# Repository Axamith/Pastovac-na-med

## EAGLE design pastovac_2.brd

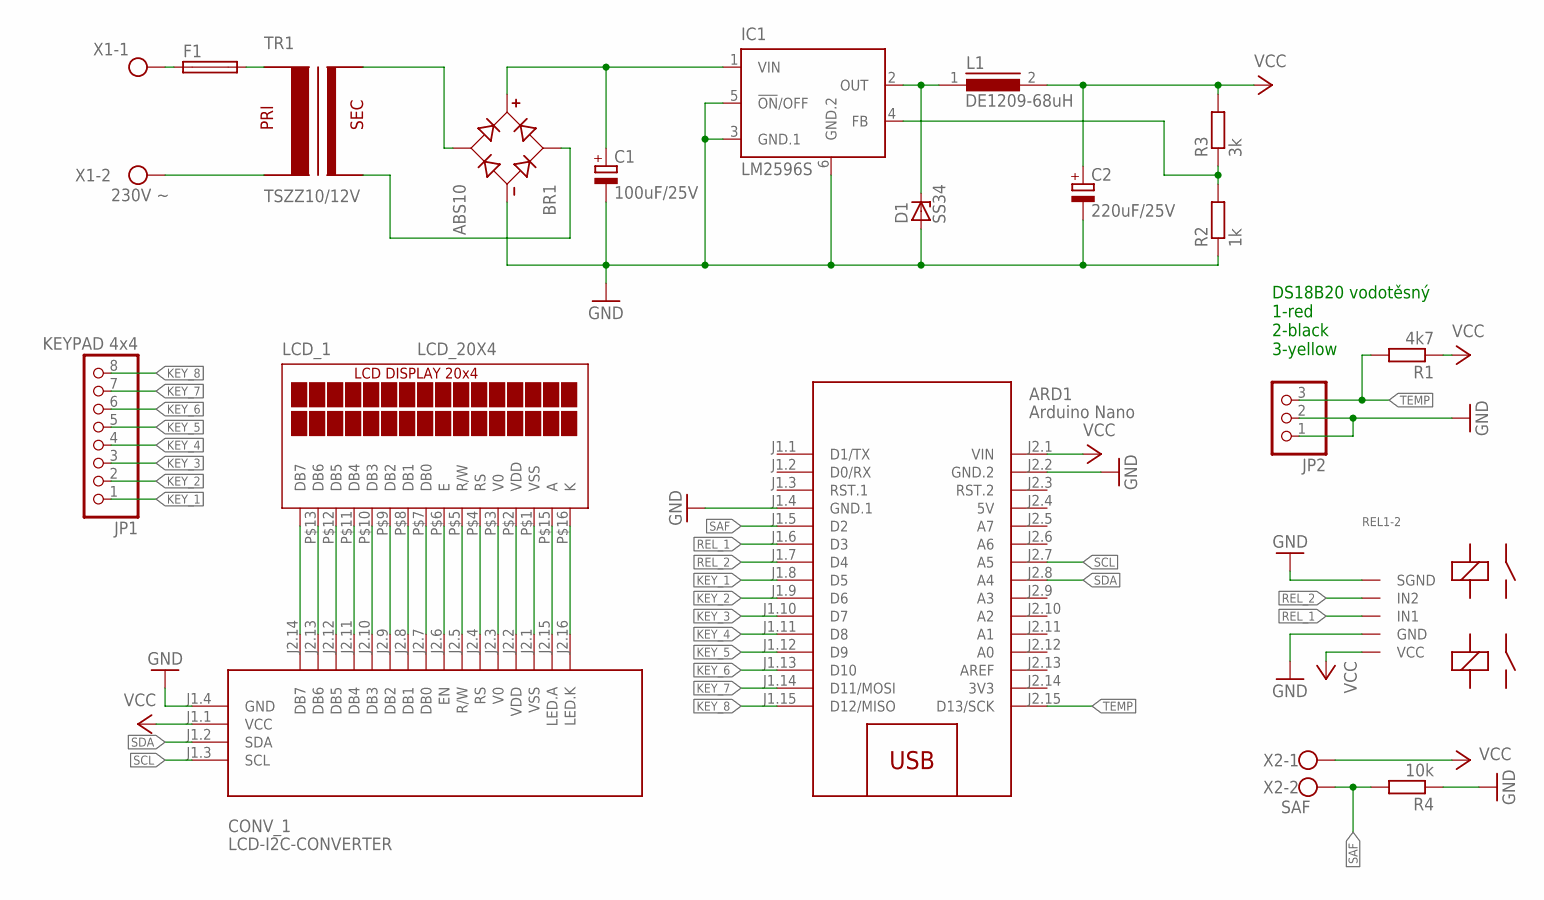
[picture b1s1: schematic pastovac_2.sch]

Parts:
ARD1: Arduino Nano; ARDUINO-NANO-3.0
BR1: ABS10; SOT200P640X160-4N
C1: 100uF/25V; 140CLH-0810
C2: 220uF/25V; 140CLH-0810
CONV_1: LCD-I2C-CONVERTER
D1: SS34; DO214AC
F1: FUSEBLANK_5X20MM; FUSE_HOLDER_5X20MM
IC1: LM2596S; TO263-5
JP1: KEYPAD 4x4; 1X08
JP2: PINHD-1X3; 1X03
L1: DE1209-68uH; DR127
LCD_1: LCD_20X4
R1: 4k7; M1206
R2: 1k; M1206
R3: 3k; M1206
R4: 10k; M1206
REL1-2: RELAY-2-5V-30A
TR1: TSZZ10/12V; TSZZ12/007M
X1: 230V ~; W237-102
X2: SAF; W237-102

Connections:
3V3: ARD1.J2.14 (3V3)
5V: ARD1.J2.4 (5V)
GND: ARD1.J1.4 (GND.1), ARD1.J2.2 (GND.2), BR1.4 (-), C1.-, C2.-, CONV_1.J1.4 (GND), D1.A, IC1.3 (GND.1), IC1.5 (!ON!/OFF), IC1.6 (GND.2), JP2.1, JP2.2, R2.1, R4.1, REL1-2.GND, REL1-2.SGND
KEY_1: ARD1.J1.8 (D5), JP1.1
KEY_2: ARD1.J1.9 (D6), JP1.2
KEY_3: ARD1.J1.10 (D7), JP1.3
KEY_4: ARD1.J1.11 (D8), JP1.4
KEY_5: ARD1.J1.12 (D9), JP1.5
KEY_6: ARD1.J1.13 (D10), JP1.6
KEY_7: ARD1.J1.14 (D11/MOSI), JP1.7
KEY_8: ARD1.J1.15 (D12/MISO), JP1.8
unnamed: CONV_1.J2.14 (DB7), LCD_1.P$14 (DB7)
unnamed: CONV_1.J2.13 (DB6), LCD_1.P$13 (DB6)
unnamed: CONV_1.J2.12 (DB5), LCD_1.P$12 (DB5)
unnamed: CONV_1.J2.11 (DB4), LCD_1.P$11 (DB4)
unnamed: CONV_1.J2.10 (DB3), LCD_1.P$10 (DB3)
unnamed: CONV_1.J2.9 (DB2), LCD_1.P$9 (DB2)
unnamed: CONV_1.J2.8 (DB1), LCD_1.P$8 (DB1)
unnamed: CONV_1.J2.7 (DB0), LCD_1.P$7 (DB0)
unnamed: CONV_1.J2.6 (EN), LCD_1.P$6 (E)
unnamed: CONV_1.J2.5 (R/W), LCD_1.P$5 (R/W)
unnamed: CONV_1.J2.4 (RS), LCD_1.P$4 (RS)
unnamed: CONV_1.J2.3 (V0), LCD_1.P$3 (V0)
unnamed: CONV_1.J2.2 (VDD), LCD_1.P$2 (VDD)
unnamed: CONV_1.J2.1 (VSS), LCD_1.P$1 (VSS)
unnamed: CONV_1.J2.15 (LED.A), LCD_1.P$15 (A)
unnamed: CONV_1.J2.16 (LED.K), LCD_1.P$16 (K)
unnamed: D1.C, IC1.2 (OUT), L1.1
unnamed: BR1.1 (AC1), TR1.P$4
unnamed: IC1.4 (FB), R2.2, R3.1
unnamed: TR1.P$2, X1.2
unnamed: F1.2, TR1.P$1
unnamed: BR1.3 (+), C1.+, IC1.1 (VIN)
unnamed: F1.1, X1.1
unnamed: BR1.2 (AC2), TR1.P$3
REL_1: ARD1.J1.6 (D3), REL1-2.IN2 (IN1)
REL_2: ARD1.J1.7 (D4), REL1-2.IN1 (IN2)
SAF: ARD1.J1.5 (D2), R4.2, X2.2
SCL: ARD1.J2.7 (A5), CONV_1.J1.3 (SCL)
SDA: ARD1.J2.8 (A4), CONV_1.J1.2 (SDA)
TEMP: ARD1.J2.15 (D13/SCK), JP2.3, R1.2
VCC: ARD1.J2.1 (VIN), C2.+, CONV_1.J1.1 (VCC), L1.2, R1.1, R3.2, REL1-2.VCC, X2.1

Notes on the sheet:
DS18B20 vodotěsný 1-red 2-black 3-yellow

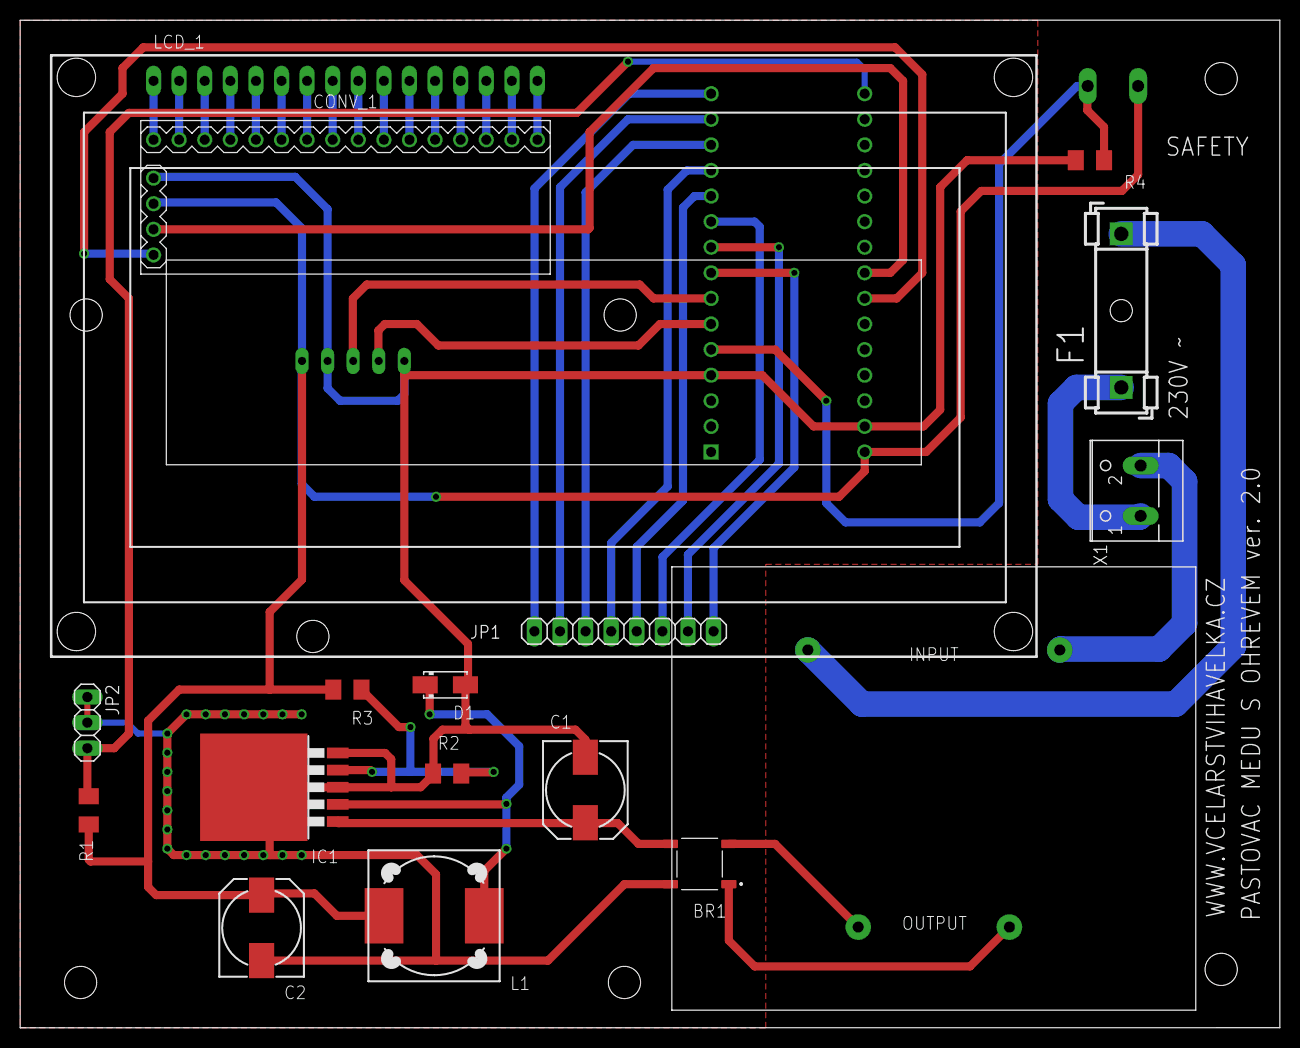
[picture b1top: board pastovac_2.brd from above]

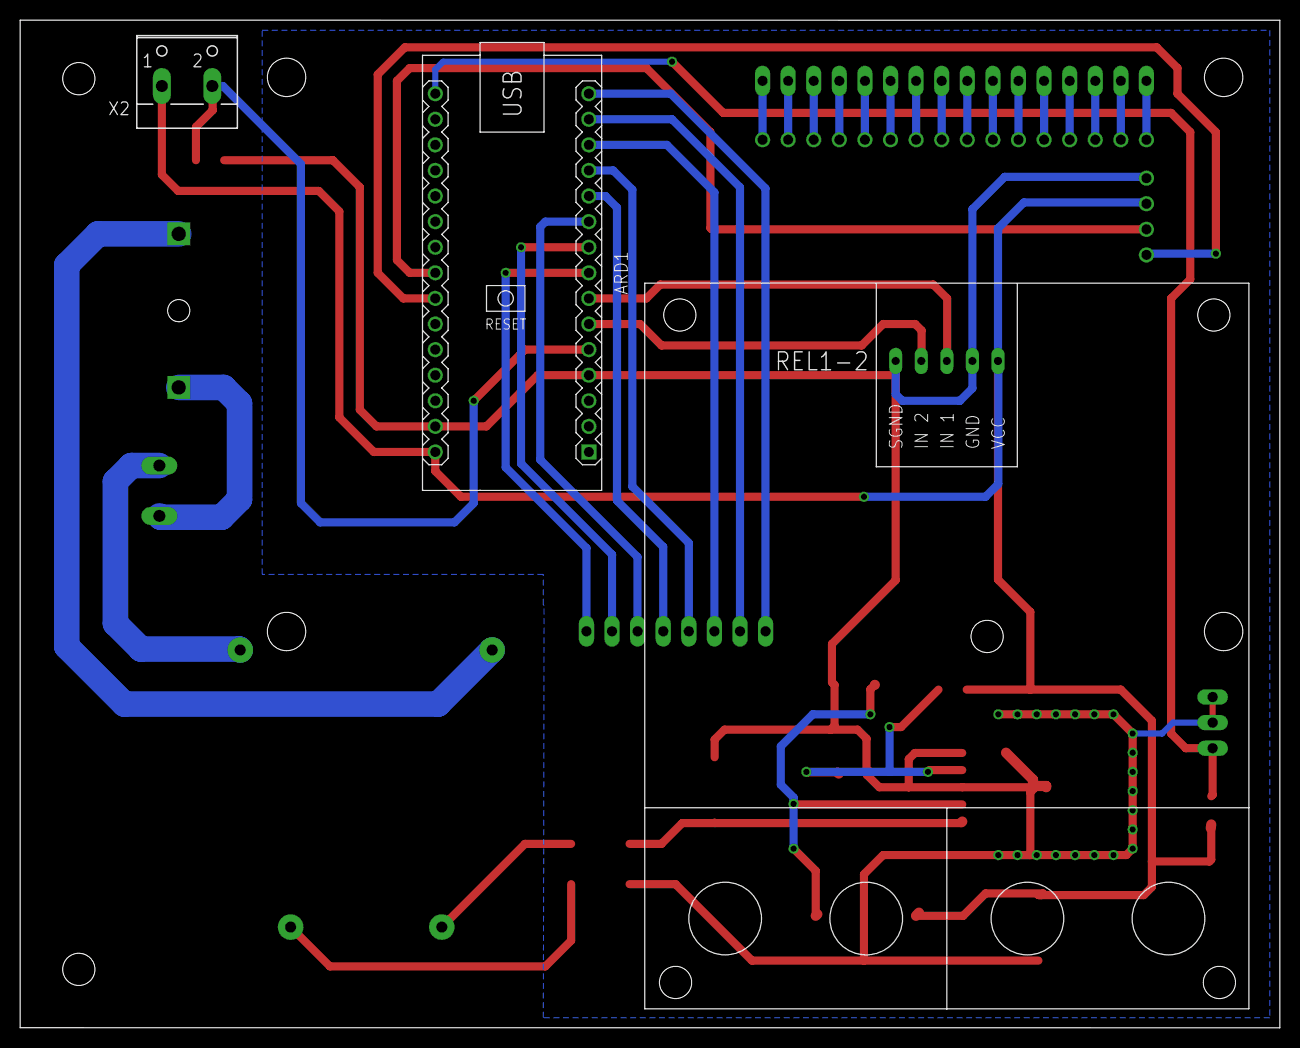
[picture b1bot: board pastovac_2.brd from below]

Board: 2 copper layers, 125.0 x 100.0 mm, 20 parts (3 on the bottom side), 40 nets.

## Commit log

2021-01-30 Create xxx

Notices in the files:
parts and their libraries:
diy-modules: Released under the Creative Commons Attribution 4.0 International License: http://creativecommons.org/licenses/by/4.0
